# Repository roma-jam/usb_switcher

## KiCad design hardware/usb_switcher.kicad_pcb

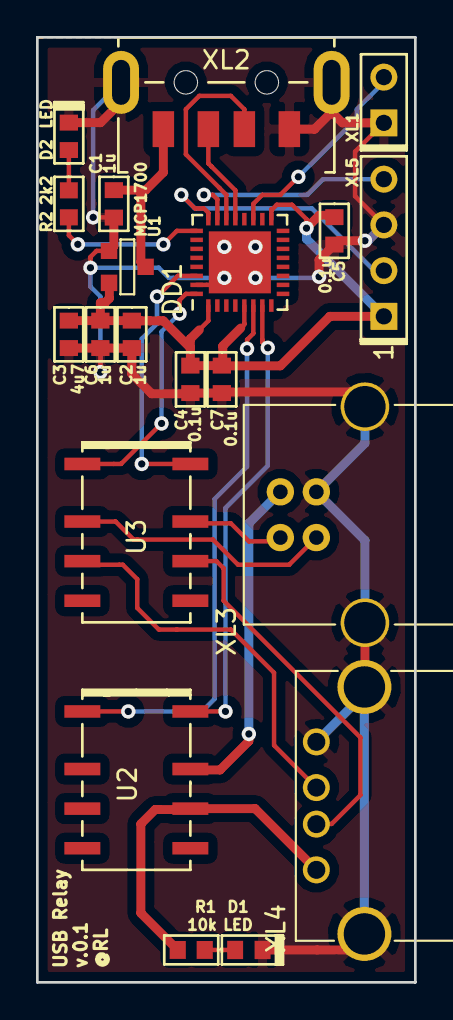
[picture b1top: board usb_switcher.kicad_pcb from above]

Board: 2 copper layers, 21.0 x 52.5 mm, 20 parts (0 on the bottom side), 21 nets.

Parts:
C1, C2, C6: 1u; CAP_0603
C3: 4u7; CAP_0603
C4, C5, C7: 0.1u; CAP_0603
D1, D2: LED; LED_0603
DD1: STM32F050K4_6; QFN-32-1EP_5x5mm_Pitch0.5mm
R1: 10k; RES_0603
R2: 2k2; RES_0603
U1: MCP1700; SOT23-3
U2, U3: IM41_3VDC; IM41_SMT_GULL_WINGS
XL1: CONN_2; PLS-2
XL2: USB_A; USB_A_Type2_PCB
XL3: USB_A; USB_B
XL4: USB_B; USB_A
XL5: ST_SWD; PLS-4

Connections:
+3.3V: C2.1, C3.1, C4.1, C5.1, C6.1, C7.1, DD1.1, DD1.5, DD1.17, U1.2, XL5.1
+5V: C1.1, U1.3, XL2.1
/DBG_TX: DD1.19, XL1.2
/DEVICE_DM: U3.6, XL4.2
/DEVICE_DP: U3.3, XL4.3
/DEVICE_POWER: R1.2, U2.6, XL4.1
/HOST_DM: U3.7, XL3.2
/HOST_DP: U3.2, XL3.3
/HOST_POWER: U2.7, XL3.1
/POWER_LED: DD1.25, R2.2
/RELAY_DATA_1: DD1.32, U3.1
/RELAY_DATA_2: DD1.30, U3.8
/RELAY_POWER_1: DD1.6, U2.1
/RELAY_POWER_2: DD1.7, U2.8
/SWCLK: DD1.24, XL5.2
/SWDIO: DD1.23, XL5.4
/USB_DM: DD1.21, XL2.2
/USB_DP: DD1.22, XL2.3
GND: C1.2, C2.2, C3.2, C4.2, C5.2, C6.2, C7.2, D1.C, D2.C, DD1.31, DD1.33, U1.1, XL1.1, XL2.4, XL2.5, XL3.4, XL3.5, XL4.4, XL4.5, XL5.3
unnamed: D1.A, R1.1
unnamed: D2.A, R2.1

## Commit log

2018-07-22 Add hardware project.
2018-07-23 Start to create PCB
2018-07-23 Complete PCB
2018-08-12 Got demo on OS. Start to write USB logic.
2018-08-13 + Fix pcd + Add gerber files
2018-08-13 + Fix git error by removing it from project settings
2018-08-14 + Try to get setup packet
2018-08-14 + Get Setup packet.
2018-08-15 + HID command switch relay on/off has done.
2018-08-15 + Add GUI program utility to control relay.
2018-08-15 Update ignore list
2018-08-15 + Made EEPROM data keeping.
2018-08-15 + Add configuration setup
2018-08-15 + Change to version 0.0.2b
2018-08-15 + Add comparing case in values.
2018-08-15 + Fix name
2018-08-15 + Make autonomous work more clearly
2018-08-16 + Add checksum to app
2018-08-16 + Add firmware update
2018-08-16 + Add GUI update FW capability
2018-08-16 + Ignore file + Remove unused commented code
2018-08-17 SOFTWARE + Add dll code example + Add library usage example
2018-08-17 + Made an alignment
2018-08-22 - Remove device state changed at power on.
2018-08-24 + Fix process freeze at 20 percent
2018-08-27 + Add binaries
2019-12-20 Firmware + Fix flash update function. + Fix timeout settings. + Add HID request for get build value for firmware update. Software + Add HID report for build value get from device. + Add 0.0.5b binary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
2022-04-19 + python example
